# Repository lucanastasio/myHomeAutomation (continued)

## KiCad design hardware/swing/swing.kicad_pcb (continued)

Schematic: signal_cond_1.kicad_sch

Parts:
C1, C6: 100n; C_0402_1005Metric
C2: 56p; C_0402_1005Metric
C3: 6.8n; C_0402_1005Metric
C4: 68p; C_0402_1005Metric
C5, C7: 1n; C_0402_1005Metric
R1, R2, R3: 220k; R_0402_1005Metric
R4: 1k; R_0402_1005Metric
R5, R10, R11: 1.5M; R_0402_1005Metric
R6, R7: 10k; R_0402_1005Metric
R8, R9: 22k; R_0402_1005Metric
RN1: 1k; R_Array_Convex_4x0402
TP1: I_{M1}; TestPoint_THTPad_D1.0mm_Drill0.5mm
TP2: I_{R1}; TestPoint_THTPad_D1.0mm_Drill0.5mm
TP3: RP_{1}; TestPoint_THTPad_D1.0mm_Drill0.5mm
U1: MCP6004; TSSOP-14_4.4x5mm_P0.65mm

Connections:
+5VA: C1.1, R6.2, U1.4 (V+); also elsewhere on the board
/CS_{1}+: RN1.2 (R2.1); also elsewhere on the board
/CS_{1}-: RN1.3 (R3.1); also elsewhere on the board
/I_{M1}: C3.1, C5.1, R4.2, TP1.1; also elsewhere on the board
/RP_{1}: R11.1, TP3.1, U1.8; also elsewhere on the board
/Signal conditioning 1/I_{R}: C4.2, R5.2, R8.1, R9.1, TP2.1, U1.14
/Signal conditioning 1/V_{REF}: R1.2, R10.2, U1.6 (-), U1.7, U1.12 (+)
unnamed: C3.2, R2.1
unnamed: R3.2, R4.1, U1.1
unnamed: R1.1, RN1.1 (R1.1), U1.3 (+)
unnamed: C2.1, RN1.7 (R2.2), RN1.8 (R1.2)
unnamed: C2.2, RN1.5 (R4.2), RN1.6 (R3.2)
unnamed: R3.1, RN1.4 (R4.1), U1.2 (-)
unnamed: C6.1, R6.1, R7.2, U1.5 (+)
unnamed: C7.2, R8.2, R10.1, U1.10 (+)
unnamed: R9.2, R11.2, U1.9 (-)
unnamed: C4.1, R2.2, R5.1, U1.13 (-)

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
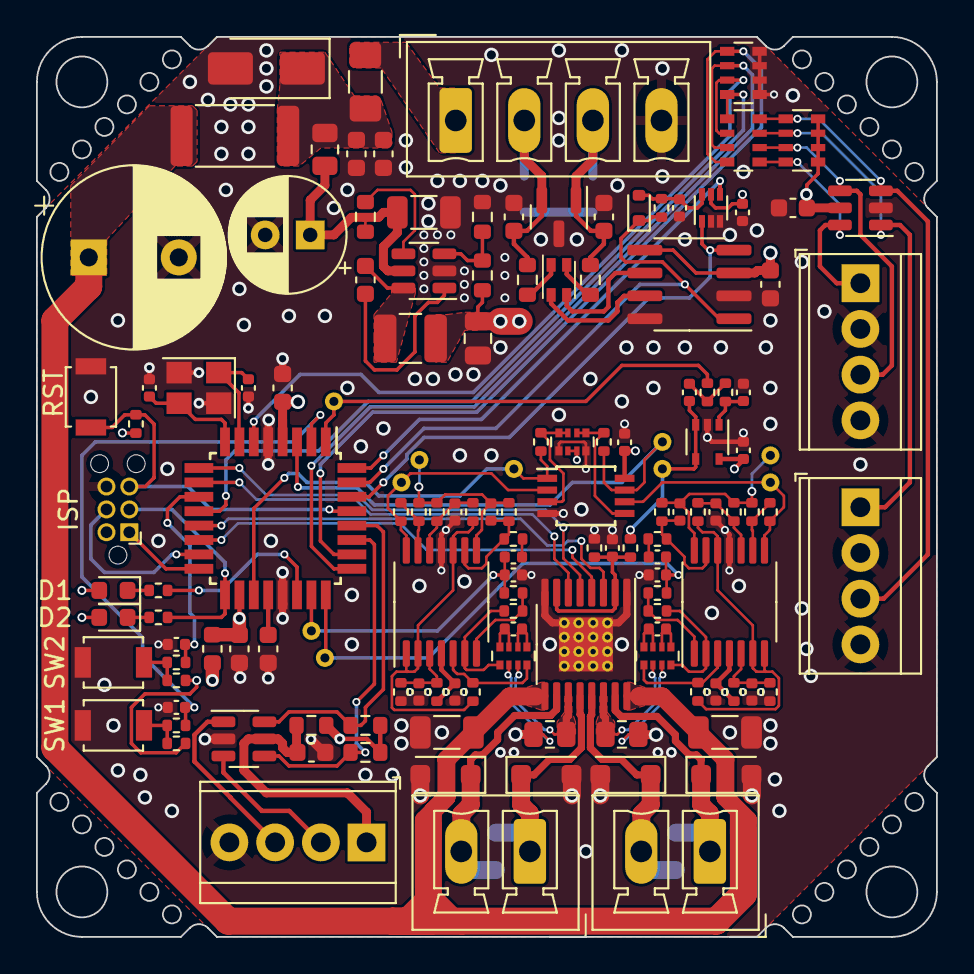
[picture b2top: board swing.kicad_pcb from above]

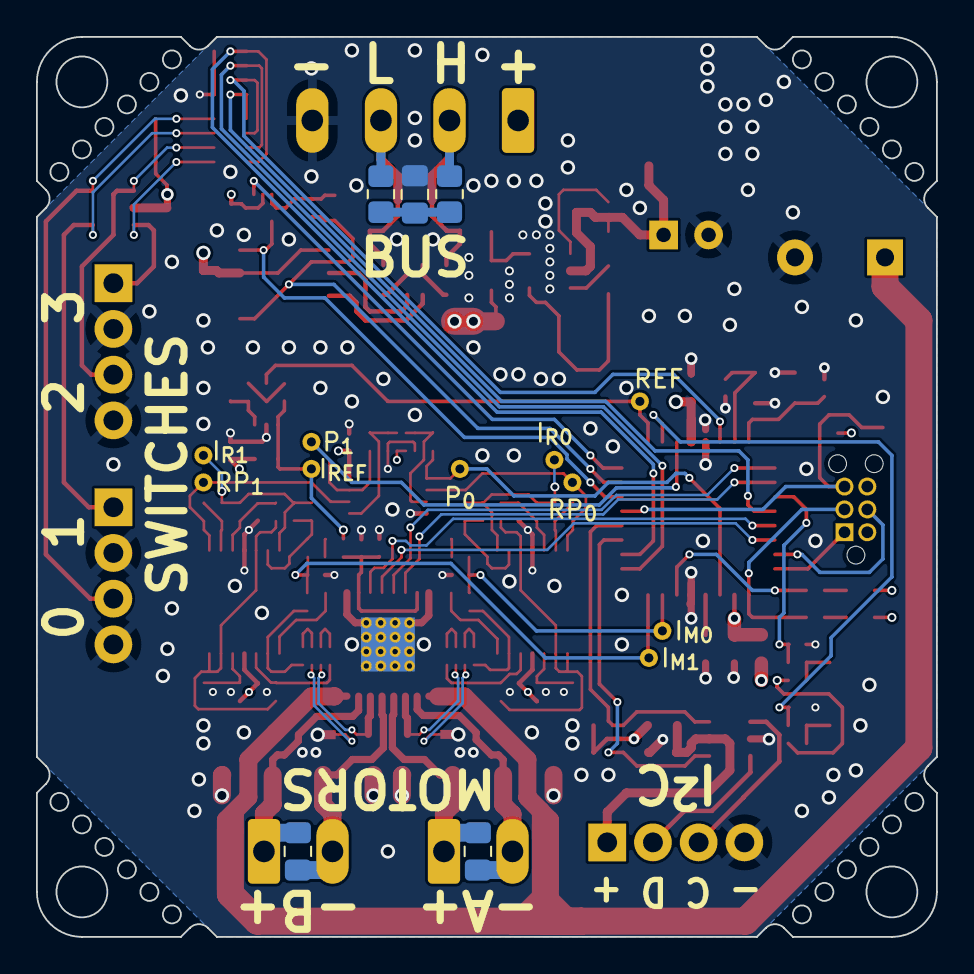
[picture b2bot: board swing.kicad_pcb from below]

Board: 4 copper layers, 50.0 x 50.0 mm, 148 parts (15 on the bottom side), 98 nets.

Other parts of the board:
J9, J11: Screw_Terminal_01x04; TerminalBlock_TE_282834-4_1x04_P2.54mm_Horizontal
